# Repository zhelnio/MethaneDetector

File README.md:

# MethaneDetector

This natural gas detector was created for using in the kitchen where a gas oven is used. It is based on MQ-4 gas sensor.
According to the sensor datasheet the standard detection conditions includes Vcc=5V±0.1 and preheat time over 24 hours. The natural gas pressure in the centralized gas supply system is very small (we don't use a gas tank). Thats why there is no need to measure the gas concentration continuously. According to this the gas sensor in this detector is working not continuous.
The typical working cycle includes: 1 minute of preheat, concentration measurements and 5 minutes of waiting. These parameters can be easily changed in the firmware source code.
For the device simplification the measurement circuit is directly connected to the ATtiny port, so the voltage on it is about 4.4V, not 5V. These conditions (maybe) reduce the MQ-4 sensitivity but it still can be used as gas detector.

**Schematic diagram**

**Board layout**

**Device photo**

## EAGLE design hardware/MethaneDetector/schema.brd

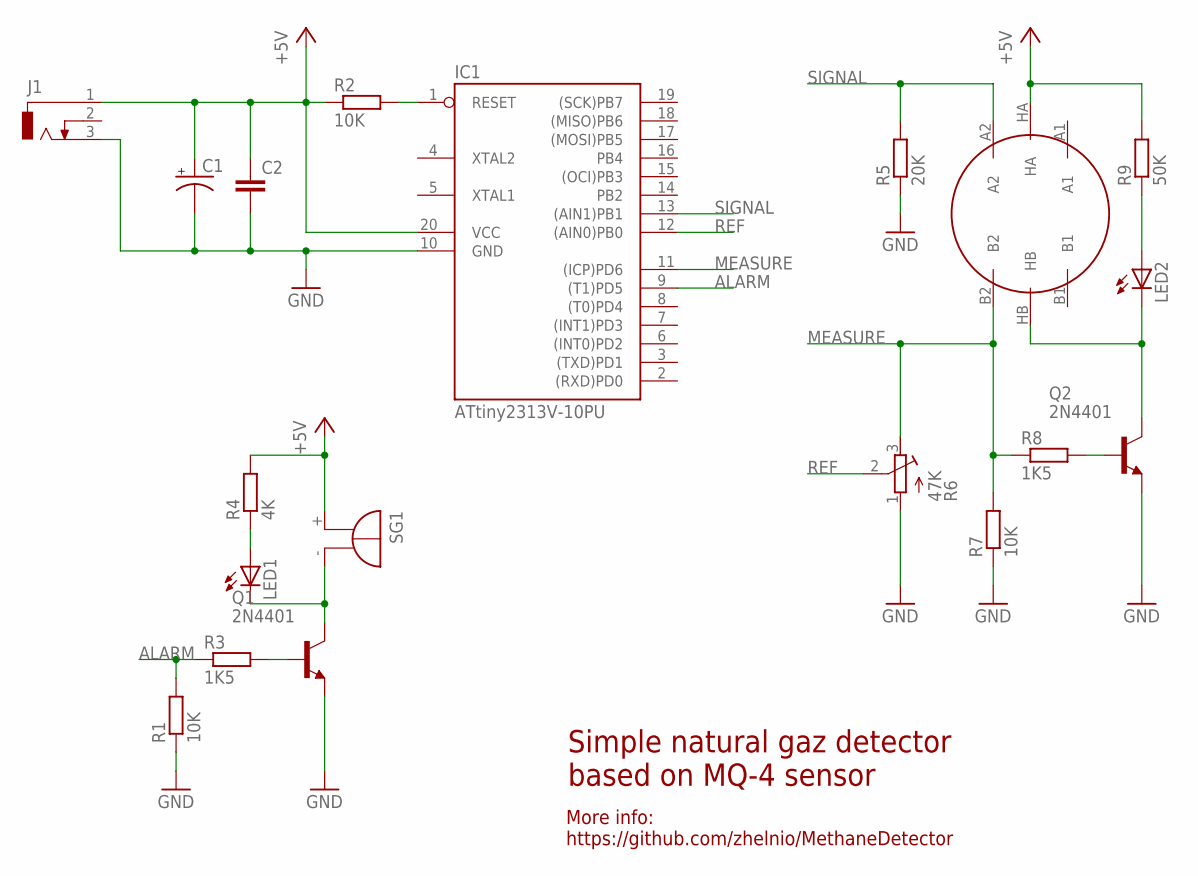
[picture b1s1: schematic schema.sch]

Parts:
C1: CPOL-USTT5D9L; TT5D9L
C2: C-EU050-030X075; C050-030X075
IC1: ATtiny2313V-10PU; DIL20
J1: DCJ0303
LED1, LED2: LED3MM
Q1, Q2: 2N4401; TO92
R1, R7: 10K; 0207/10
R2: 10K; 0204/7
R3, R8: 1K5; 0207/10
R4: 4K; 0207/10
R5: 20K; 0207/10
R6: 47K; RTRIM3296W
R9: 50K; 0207/10
SEN1: METHANE_SENSOR; MQ-3
SG1: BMT1205XH7.5

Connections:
+5V: C1.+, C2.1, IC1.20 (VCC), J1.1, R2.1, R4.2, R9.2, SEN1.HA, SG1.+
ALARM: IC1.9 ((T1)PD5), R1.2, R3.1
GND: C1.-, C2.2, IC1.10 (GND), J1.3, Q1.3 (E), Q2.3 (E), R1.1, R5.1, R6.1 (A), R7.1
MEASURE: IC1.11 ((ICP)PD6), R6.3 (E), R7.2, R8.1, SEN1.B2
unnamed: LED1.K (C), Q1.1 (C), SG1.-
unnamed: IC1.1 (RESET), R2.2
unnamed: LED1.A, R4.1
unnamed: Q1.2 (B), R3.2
unnamed: Q2.2 (B), R8.2
unnamed: LED2.K (C), Q2.1 (C), SEN1.HB
unnamed: LED2.A, R9.1
REF: IC1.12 ((AIN0)PB0), R6.2 (S)
SIGNAL: IC1.13 ((AIN1)PB1), R5.2, SEN1.A2

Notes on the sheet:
Simple natural gaz detector based on MQ-4 sensor
More info: https://github.com/zhelnio/MethaneDetector

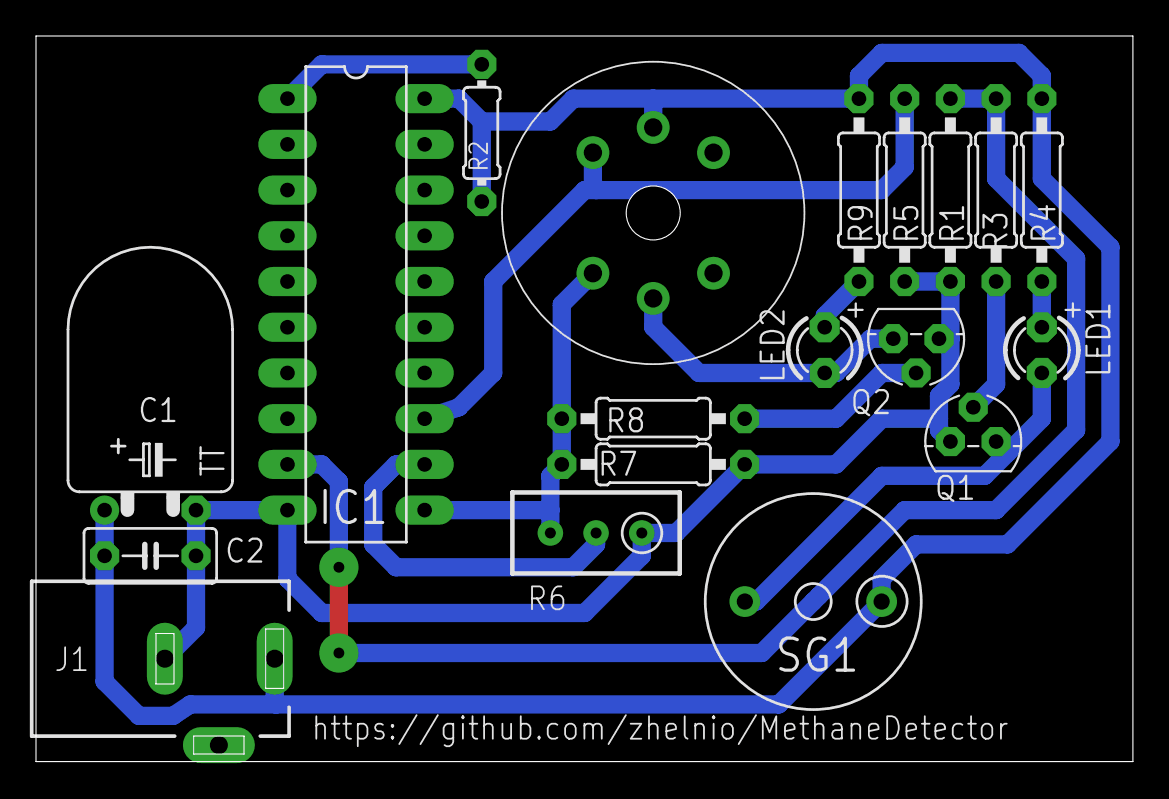
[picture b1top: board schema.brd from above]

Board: 2 copper layers, 60.9 x 40.3 mm, 19 parts (0 on the bottom side), 13 nets.

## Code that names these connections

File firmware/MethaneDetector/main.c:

/*
MIT License

Copyright (c) 2016 Stanislav Zhelnio

Permission is hereby granted, free of charge, to any person obtaining a copy
of this software and associated documentation files (the "Software"), to deal
in the Software without restriction, including without limitation the rights
to use, copy, modify, merge, publish, distribute, sublicense, and/or sell
copies of the Software, and to permit persons to whom the Software is
furnished to do so, subject to the following conditions:

The above copyright notice and this permission notice shall be included in all
copies or substantial portions of the Software.

THE SOFTWARE IS PROVIDED "AS IS", WITHOUT WARRANTY OF ANY KIND, EXPRESS OR
IMPLIED, INCLUDING BUT NOT LIMITED TO THE WARRANTIES OF MERCHANTABILITY,
FITNESS FOR A PARTICULAR PURPOSE AND NONINFRINGEMENT. IN NO EVENT SHALL THE
AUTHORS OR COPYRIGHT HOLDERS BE LIABLE FOR ANY CLAIM, DAMAGES OR OTHER
LIABILITY, WHETHER IN AN ACTION OF CONTRACT, TORT OR OTHERWISE, ARISING FROM,
OUT OF OR IN CONNECTION WITH THE SOFTWARE OR THE USE OR OTHER DEALINGS IN THE
SOFTWARE.
 */ 

#define F_CPU 1000000UL

#include <avr/io.h>
#include <avr/interrupt.h>
#include <util/delay.h>
#include <stdbool.h>
#include <avr/sleep.h>

/*
	PB1 (AIN1)	- detector signal
	PB0 (AIN0)	- reference
	PD6			- detector on/off
	PD5			- alarm on/off
*/

#pragma region HAL

inline void init(void)
{
	//set ports to out
	PORTD = 0;
	DDRD = (1 << DDD5) | (1 << DDD6);

	//disable digital input on comparator pins
	DIDR = (1 << AIN1D) | (1 << AIN0D);

	//timer init
	TCCR1A = 0;
	TCCR1B = (1 << WGM12)| (1 << CS12) | (1 << CS10); // clk/1024, CTC mode
	TCCR1C = 0;
	OCR1A  = 488;			// T = 0.5 sec
	OCR1B  = 0;
	TIMSK  = (1 << OCIE1A);	// interrupt on overflow

	set_sleep_mode(SLEEP_MODE_IDLE);

	//enable interrupts
	sei();
}

// I'm using active buzzer so there is no PWM or something else for Alarm signal
inline void turnAlarmOn(void)		{ PORTD |= (1 << PD5);  } 
inline void turnAlarmOff(void)		{ PORTD &= ~(1 << PD5); }
inline void turnDetectorOn(void)	{ PORTD |= (1 << PD6);	}
inline void turnDetectorOff(void)	{ PORTD &= ~(1 << PD6);	}
inline bool getSensorValue(void)	{ return !(ACSR & (1 << ACO));	}


#pragma endregion HAL

#pragma region input filter

// if we have some noise, then gas detected
#define FILTER_WINDOW_SIZE 16

bool gasDetected(void)
{
	for(uint8_t i = 0; i < FILTER_WINDOW_SIZE; i++)
		if(getSensorValue())
			return true;
	return false;
}

#pragma endregion input filter

#pragma region Sound

// 8 notes are playing for each sound: one per bit
typedef enum {SoundInitDone = 0b00000101, SoundAlarm = 0b00111001, SoundNone = 0 } Sound;
Sound	nextSound = 0;

inline void setDiscreteSound(Sound sound)
{
	nextSound = sound;
}

inline Sound getDiscreteSound(void)
{
	Sound s = nextSound;
	nextSound = SoundNone;	
	return s;
}

void playDiscreteSound()
{
	static uint8_t currentSound = 0;
	static uint8_t soundNoteNum = 8;

	if(soundNoteNum == 8)
	{
		currentSound = getDiscreteSound();
		soundNoteNum = 0;
	}
	else
	{
		if(currentSound & (1 << soundNoteNum++))
			turnAlarmOn();
		else
			turnAlarmOff();
	}
}
#pragma endregion Sound

#pragma region FSM

//periods of sensor preheat before detection and waiting after
#define HEAT_PERIOD 60
#define WAIT_PERIOD 300

#define TIMER_TICKS_IN_SECOND 2

/*
FSM states:
	INIT	- first step
	HEAT	- enable heater in sensor and wait
	DETECT	- check sensor value
	ALARM	- gas detected, enable alarm sound
	WAIT	- sensor heater disabled

    INIT -> HEAT -> DETECT -.
             ^        |     |
             |        |     |
            WAIT <----'     |
             ^              |
             |              |
            ALARM <---------'
             ^  |
             ''''
*/

typedef enum {Init, Heat, Detect, Alarm, Wait } FsmState;

inline FsmState getNextState(FsmState state, uint16_t currentStateDelay)
{	
	switch (state)
	{
		default:
		case Init:		return Heat;
		case Heat:		return (currentStateDelay) ? Heat : Detect;
		case Detect:	return gasDetected() ? Alarm : Wait;
		case Wait:		return (currentStateDelay) ? Wait : Heat;
		case Alarm:		return gasDetected() ? Alarm : Wait;
	}
}

uint16_t getStateDelay(FsmState state)
{
	switch (state)
	{
		default:
		case Init:		return 0;
		case Heat:		return HEAT_PERIOD * TIMER_TICKS_IN_SECOND;
		case Detect:	return 0;
		case Wait:		return WAIT_PERIOD * TIMER_TICKS_IN_SECOND;
		case Alarm:		return 0;
	}
}

inline void setStateOutput(FsmState state)
{
	switch (state)
	{
		case Init:		break;
		case Heat:		turnDetectorOn(); break;
		case Detect:	break;
		case Wait:		turnDetectorOff(); break;
		case Alarm:		setDiscreteSound(SoundAlarm); break;
	}
}

void fsm(void)
{
	static FsmState State = Init;
	static uint16_t currentStateDelay = 0;

	FsmState Next = getNextState(State, currentStateDelay);
	currentStateDelay = (currentStateDelay > 0) ? (currentStateDelay - 1) : getStateDelay(Next);

	State = Next;
	setStateOutput(State);
}
#pragma endregion FSM

int main(void)
{
	init();

	turnDetectorOn();

	setDiscreteSound(SoundInitDone);

	while (1)
		sleep_mode();
}

ISR(TIMER1_COMPA_vect)
{
	playDiscreteSound();

	fsm();
}

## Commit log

2016-09-18 init
2016-09-18 hw and fw added
2016-09-18 small fix
2016-09-18 readme update
2016-09-18 small change
2016-09-18 github lang change
2016-09-18 component docs added
2016-09-19 small component name fix

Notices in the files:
parts and their libraries:
SparkFun-Sensors: Licensing: Creative Commons ShareAlike 4.0 International - https://creativecommons.org/licenses/by-sa/4.0
